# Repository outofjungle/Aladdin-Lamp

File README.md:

# Aladdin-Lamp

## Top

## Bottom

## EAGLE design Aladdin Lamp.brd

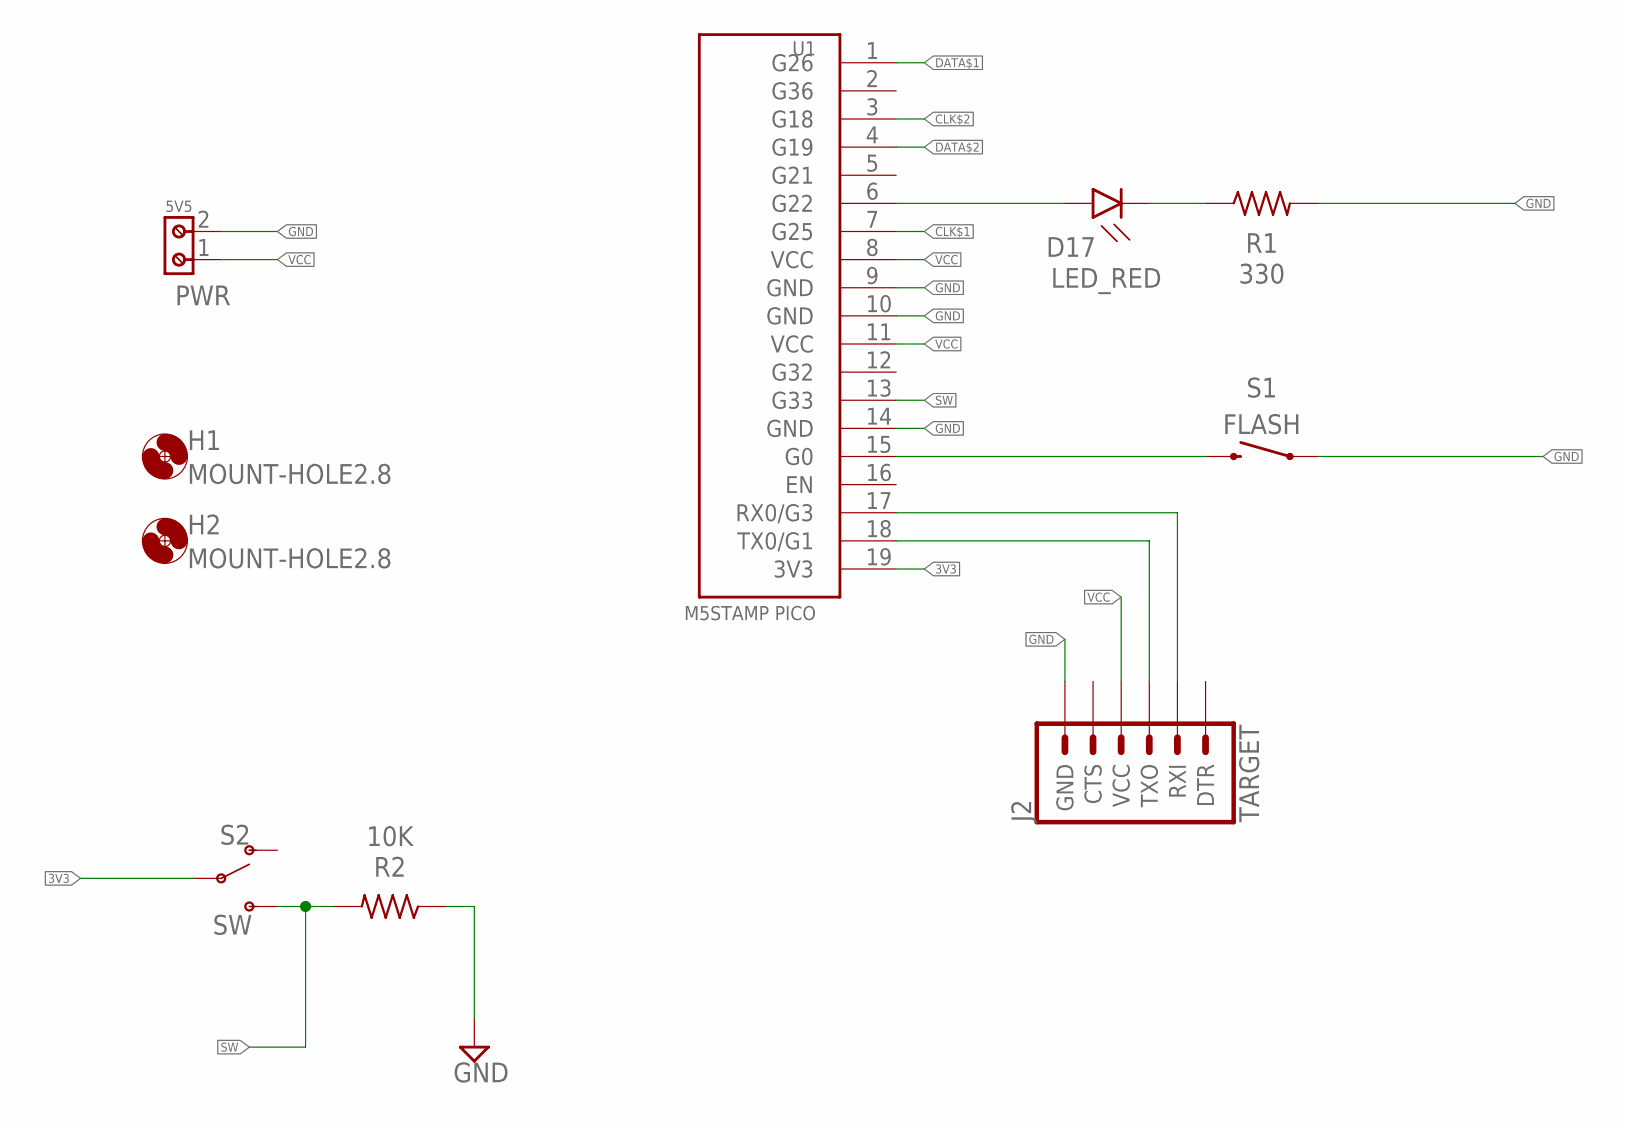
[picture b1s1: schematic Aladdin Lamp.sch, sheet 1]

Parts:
D17: LED_RED; LEDC2012X110N_FLAT-R
H1, H2: MOUNT-HOLE2.8; 2,8
J2: TARGET; 6_PIN_SERIAL_TARGET_SIDE_W_SILK
PWR: 5V5; 691213510002
R1: 330; RESC2012X65
R2: 10K; RESC2012X65
S1: FLASH; TACTILE_SWITCH_SMD_5.2MM
S2: SW; SWITCH_SPST_SMD_A
U1: M5STAMP PICO; M5STAMP-PICO

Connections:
3V3: S2.2, U1.19 (3V3)
CLK$1: U1.7 (G25); also elsewhere on the board
CLK$2: U1.3 (G18); also elsewhere on the board
DATA$1: U1.1 (G26); also elsewhere on the board
DATA$2: U1.4 (G19); also elsewhere on the board
G0: S1.3 (2), U1.15 (G0)
GND: J2.P$6 (GND), PWR.2, R1.2, R2.1, S1.1, U1.9 (GND), U1.10 (GND), U1.14 (GND); also elsewhere on the board
RX: J2.P$3 (RXI), U1.17 (RX0/G3)
SATUS_LED$1: D17.A, U1.6 (G22)
SATUS_LED$2: D17.C, R1.1
SW: R2.2, S2.3 (S), U1.13 (G33)
TX: J2.P$2 (TXO), U1.18 (TX0/G1)
VCC: J2.P$4 (VCC), PWR.1, U1.8 (VCC), U1.11 (VCC); also elsewhere on the board

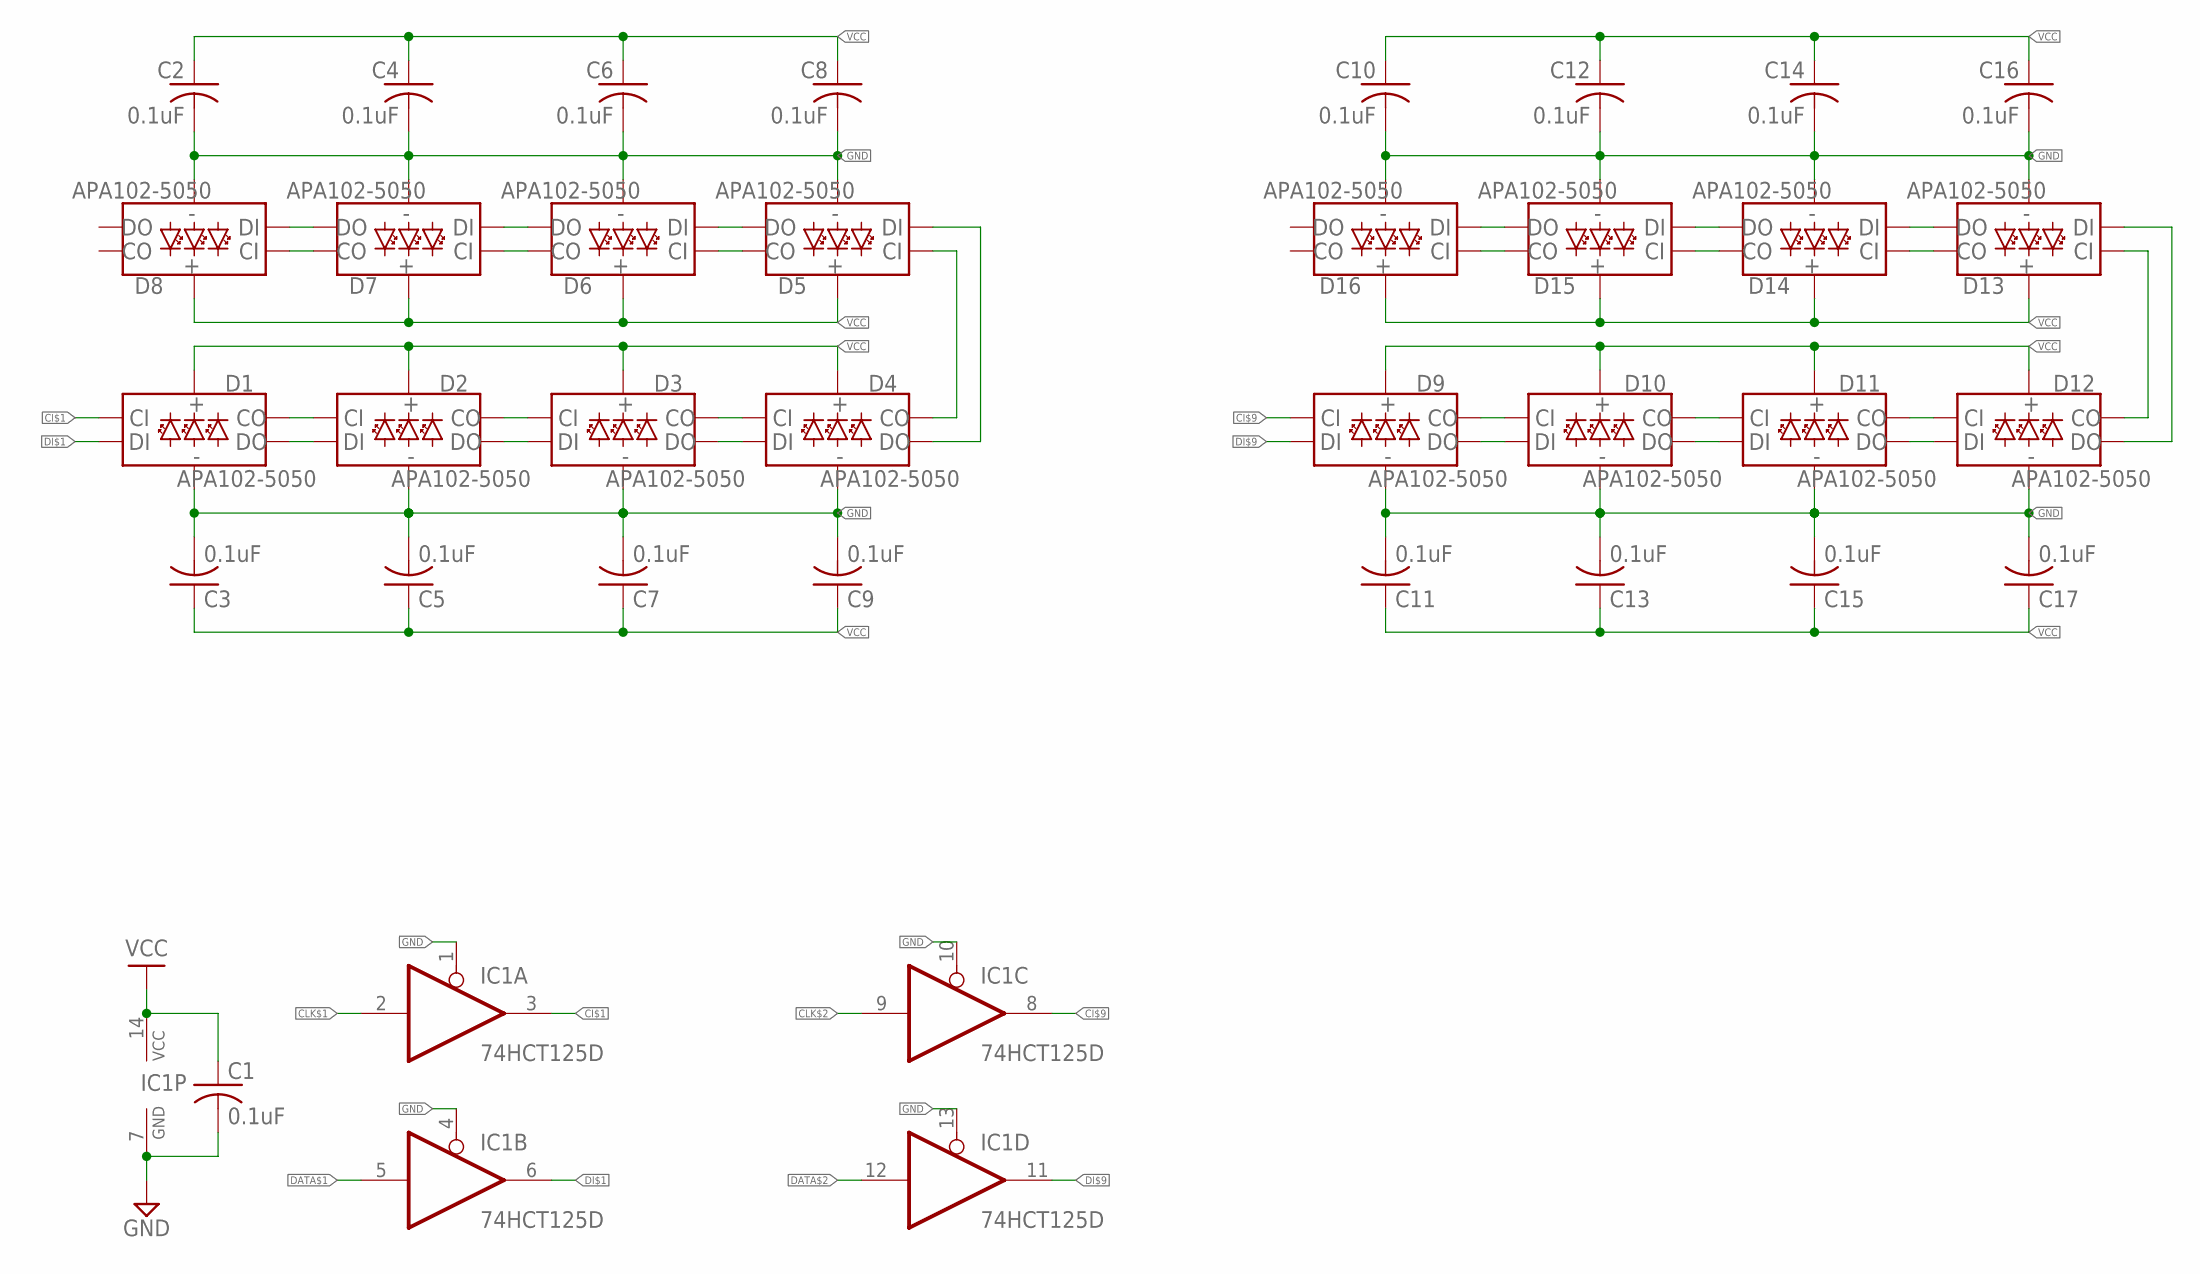
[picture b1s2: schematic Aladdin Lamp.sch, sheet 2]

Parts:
C1, C2, C3, C4, C5, C6, C7, C8, C9, C10, C11, C12, C13, C14, C15, C16, C17: 0.1uF; CAPC2012X110
D1, D2, D3, D4, D5, D6, D7, D8, D9, D10, D11, D12, D13, D14, D15, D16: APA102-5050
IC1: 74HCT125D; SO14

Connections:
CI$1: D1.P2 (CI), IC1.3 (O)
CI$2: D1.P5 (CO), D2.P2 (CI)
CI$3: D2.P5 (CO), D3.P2 (CI)
CI$4: D3.P5 (CO), D4.P2 (CI)
CI$5: D4.P5 (CO), D5.P2 (CI)
CI$6: D5.P5 (CO), D6.P2 (CI)
CI$7: D6.P5 (CO), D7.P2 (CI)
CI$8: D7.P5 (CO), D8.P2 (CI)
CI$9: D9.P2 (CI), IC1.8 (O)
CI$10: D9.P5 (CO), D10.P2 (CI)
CI$11: D10.P5 (CO), D11.P2 (CI)
CI$12: D11.P5 (CO), D12.P2 (CI)
CI$13: D12.P5 (CO), D13.P2 (CI)
CI$14: D13.P5 (CO), D14.P2 (CI)
CI$15: D14.P5 (CO), D15.P2 (CI)
CI$16: D15.P5 (CO), D16.P2 (CI)
CLK$1: IC1.2 (I); also elsewhere on the board
CLK$2: IC1.9 (I); also elsewhere on the board
DATA$1: IC1.5 (I); also elsewhere on the board
DATA$2: IC1.12 (I); also elsewhere on the board
DI$1: D1.P1 (DI), IC1.6 (O)
DI$2: D1.P6 (DO), D2.P1 (DI)
DI$3: D2.P6 (DO), D3.P1 (DI)
DI$4: D3.P6 (DO), D4.P1 (DI)
DI$5: D4.P6 (DO), D5.P1 (DI)
DI$6: D5.P6 (DO), D6.P1 (DI)
DI$7: D6.P6 (DO), D7.P1 (DI)
DI$8: D7.P6 (DO), D8.P1 (DI)
DI$9: D9.P1 (DI), IC1.11 (O)
DI$10: D9.P6 (DO), D10.P1 (DI)
DI$11: D10.P6 (DO), D11.P1 (DI)
DI$12: D11.P6 (DO), D12.P1 (DI)
DI$13: D12.P6 (DO), D13.P1 (DI)
DI$14: D13.P6 (DO), D14.P1 (DI)
DI$15: D14.P6 (DO), D15.P1 (DI)
DI$16: D15.P6 (DO), D16.P1 (DI)
GND: C1.2, C2.2, C3.2, C4.2, C5.2, C6.2, C7.2, C8.2, C9.2, C10.2, C11.2, C12.2, C13.2, C14.2, C15.2, C16.2, C17.2, D1.P3 (GND), D2.P3 (GND), D3.P3 (GND), D4.P3 (GND), D5.P3 (GND), D6.P3 (GND), D7.P3 (GND), D8.P3 (GND), D9.P3 (GND), D10.P3 (GND), D11.P3 (GND), D12.P3 (GND), D13.P3 (GND), D14.P3 (GND), D15.P3 (GND), D16.P3 (GND), IC1.1 (OE), IC1.4 (OE), IC1.7 (GND), IC1.10 (OE), IC1.13 (OE); also elsewhere on the board
VCC: C1.1, C2.1, C3.1, C4.1, C5.1, C6.1, C7.1, C8.1, C9.1, C10.1, C11.1, C12.1, C13.1, C14.1, C15.1, C16.1, C17.1, D1.P4 (VCC), D2.P4 (VCC), D3.P4 (VCC), D4.P4 (VCC), D5.P4 (VCC), D6.P4 (VCC), D7.P4 (VCC), D8.P4 (VCC), D9.P4 (VCC), D10.P4 (VCC), D11.P4 (VCC), D12.P4 (VCC), D13.P4 (VCC), D14.P4 (VCC), D15.P4 (VCC), D16.P4 (VCC), IC1.14 (VCC); also elsewhere on the board

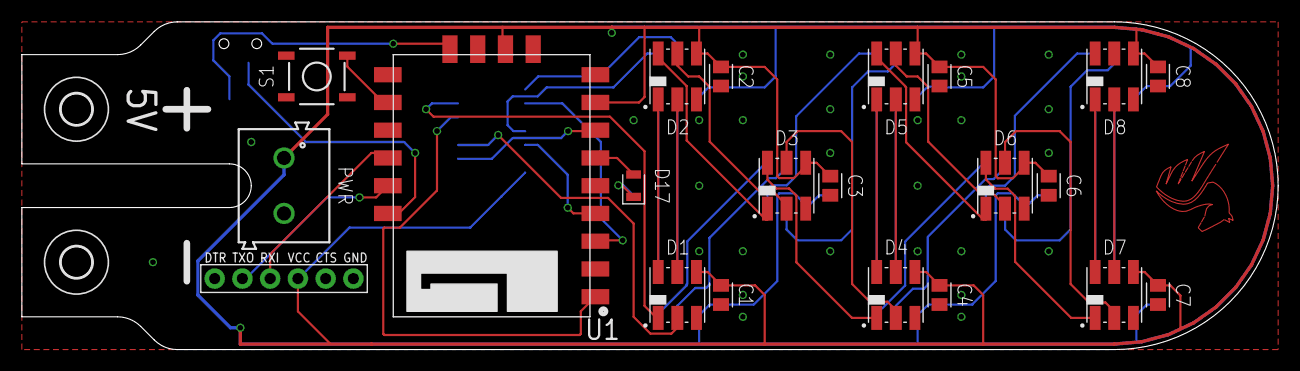
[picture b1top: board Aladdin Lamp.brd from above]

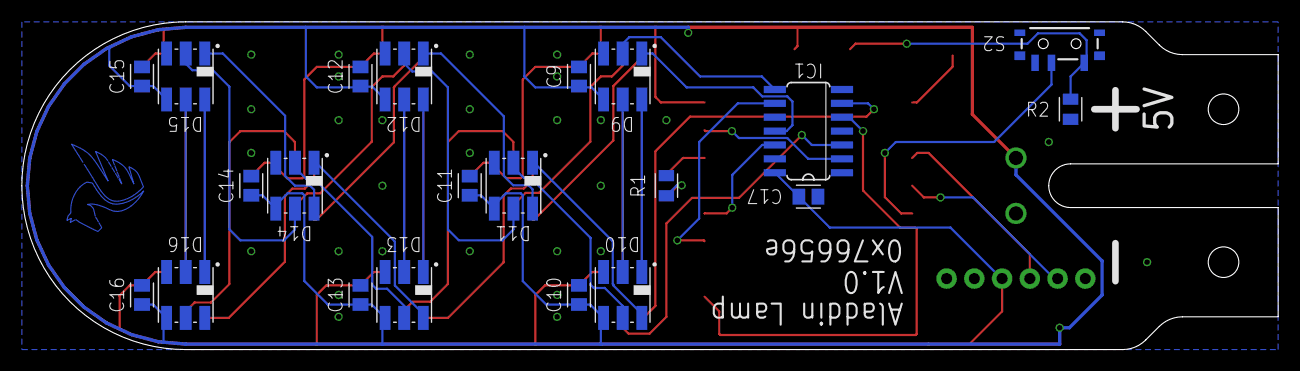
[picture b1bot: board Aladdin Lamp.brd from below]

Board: 2 copper layers, 115.0 x 30.0 mm, 44 parts (21 on the bottom side), 45 nets.

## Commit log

2022-10-11 cosmetic changes
2022-10-23 final v1.0
2025-12-16 added schematic diagram

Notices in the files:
parts and their libraries:
SparkFun-LED: Licensing: Creative Commons ShareAlike 4.0 International - https://creativecommons.org/licenses/by-sa/4.0
Wurth_Connectors_WR-TBL Rising Cage Clam: Copyright: Würth Elektronik
